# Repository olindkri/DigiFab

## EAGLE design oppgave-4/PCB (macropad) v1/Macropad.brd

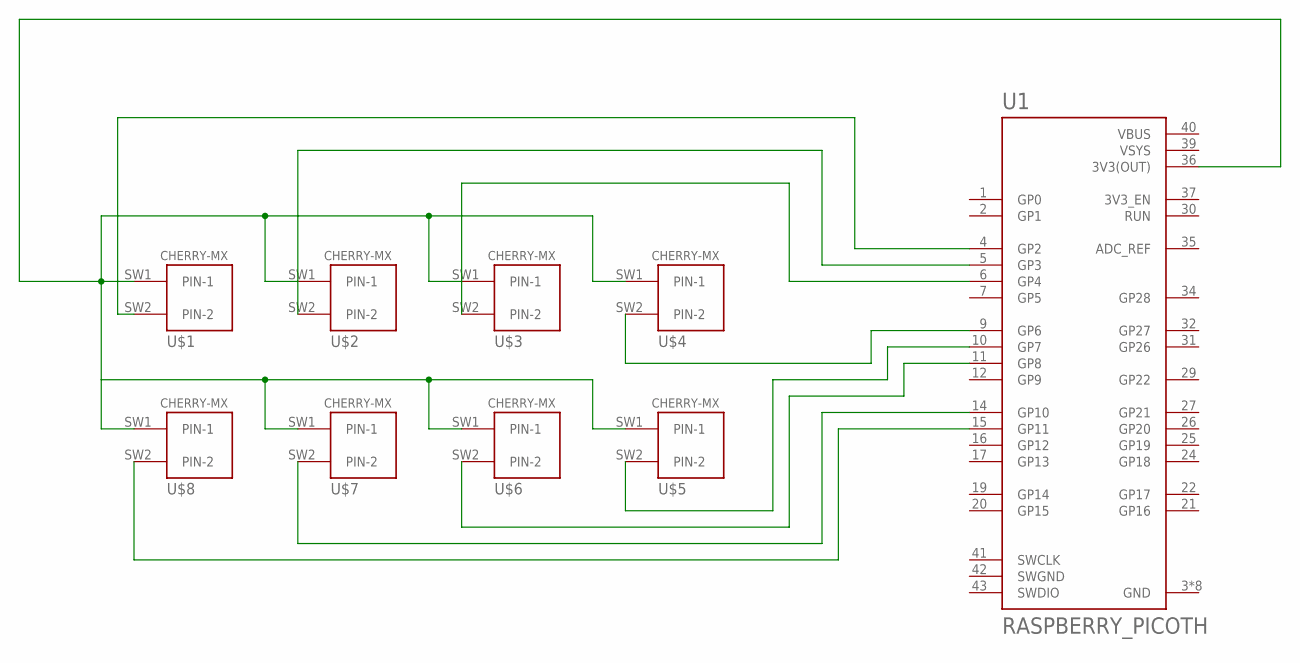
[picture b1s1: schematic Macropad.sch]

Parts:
U1: RASPBERRY_PICOTH; PICO-PKG-TH
U$1, U$2, U$3, U$4, U$5, U$6, U$7, U$8: CHERRY-MX

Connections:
GND: U1.3 (GND), U1.8 (GND), U1.13 (GND), U1.18 (GND), U1.23 (GND), U1.28 (GND), U1.33 (GND), U1.38 (GND)
unnamed: U1.9 (GP6), U$4.SW2 (PIN-2)
unnamed: U1.36 (3V3(OUT)), U$1.SW1 (PIN-1), U$2.SW1 (PIN-1), U$3.SW1 (PIN-1), U$4.SW1 (PIN-1), U$5.SW1 (PIN-1), U$6.SW1 (PIN-1), U$7.SW1 (PIN-1), U$8.SW1 (PIN-1)
unnamed: U1.6 (GP4), U$3.SW2 (PIN-2)
unnamed: U1.5 (GP3), U$2.SW2 (PIN-2)
unnamed: U1.4 (GP2), U$1.SW2 (PIN-2)
unnamed: U1.10 (GP7), U$5.SW2 (PIN-2)
unnamed: U1.11 (GP8), U$6.SW2 (PIN-2)
unnamed: U1.14 (GP10), U$7.SW2 (PIN-2)
unnamed: U1.15 (GP11), U$8.SW2 (PIN-2)
SWGND: U1.42 (SWGND)
VBUS: U1.40 (VBUS)
VSYS: U1.39 (VSYS)

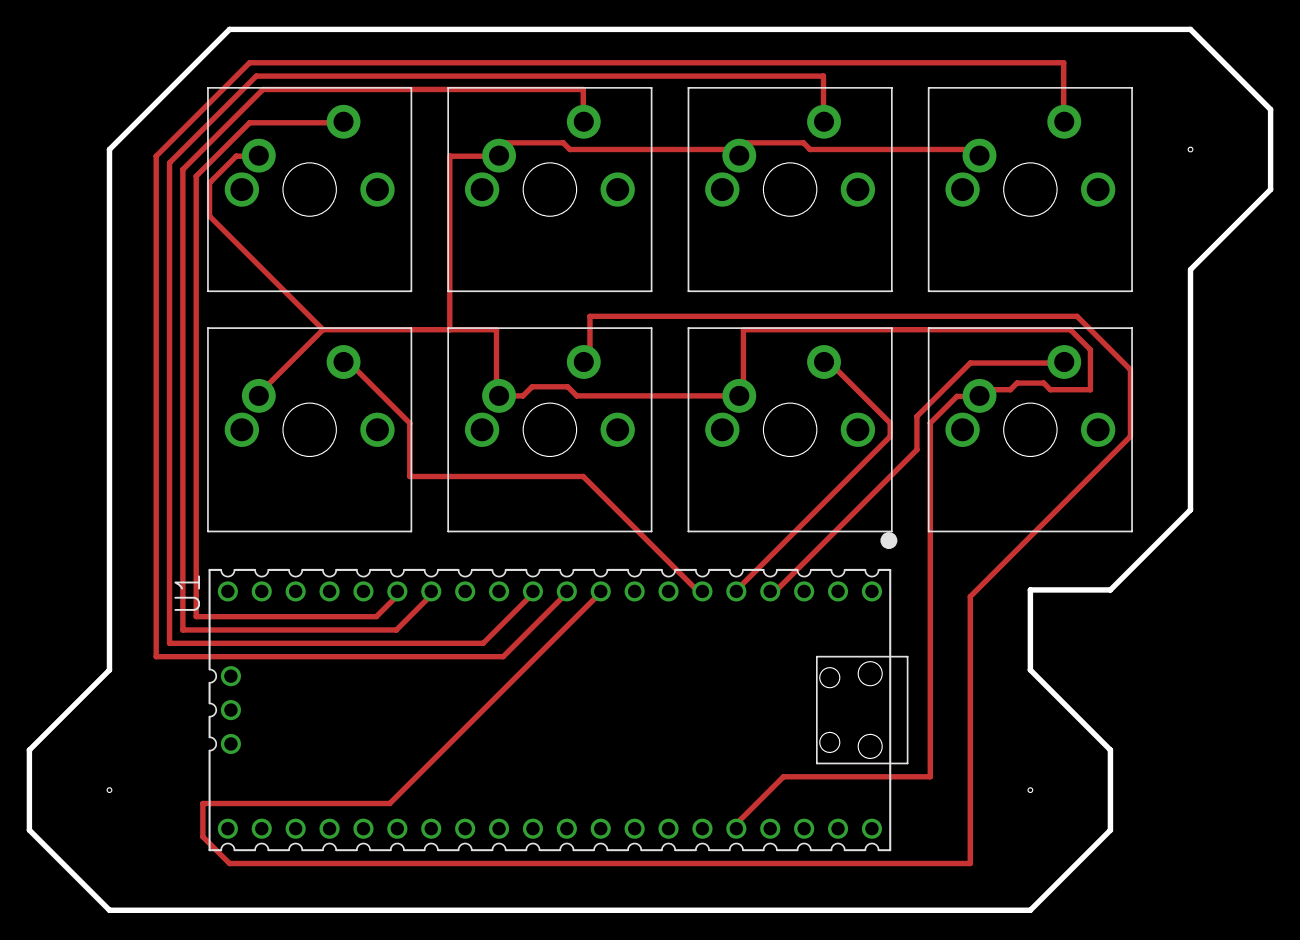
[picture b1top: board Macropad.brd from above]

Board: 2 copper layers, 93.0 x 66.0 mm, 9 parts (0 on the bottom side), 10 nets.

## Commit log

2022-09-28 added files
    added files.
2022-09-28 added more files
2022-09-29 added new css and other changes
2022-09-30 started on portfolio
2022-10-01 many changes, formating, design, etc. prob done
2022-10-01 fixed universal layout
2022-10-01 finito
2022-10-02 finito finito
2022-11-25 images and notes
    (:
2022-11-25 f3d file
    (:
2022-11-25 folder structure
    (:
2022-11-25 Added oppgave 2
    (:
2023-02-15 added oblig3
2023-02-15 update website
2023-03-16 updated "oppgave-2"
    Added "ver-2" of the macropad.
2023-03-20 oblig-4
2023-03-20 updated oblig-4
2023-03-21 Eagle filer
    Schema og .brd fil
2023-03-23 PDF fil
2023-03-23 THEME CHANGE
2023-03-23 THEME CHANGES
2023-05-16 updated color palette and task status.
2023-05-17 fixed overscroll color
2023-05-17 macos/ios theme color
2023-05-25 pdf file (with code and video)
2023-05-25 updated site
2023-05-25 endret PDF
2023-05-29 Added PCB schematic
2023-05-30 added fusion 360 file
2023-05-30 Added code files
    code.py is the used code for the macropad (since the OLED got defect) oled.py is the code that worked containing oled functionality. R-encoder.py has added code for a rotary encoder (not included for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
2023-05-30 Rename oled.py to code1.py
2023-05-30 Rename code.py to encoder.py
2023-05-30 Rename code1.py to code.py
2023-05-30 Rename R-encoder.py to oled.py
2023-06-08 minimal design changes
